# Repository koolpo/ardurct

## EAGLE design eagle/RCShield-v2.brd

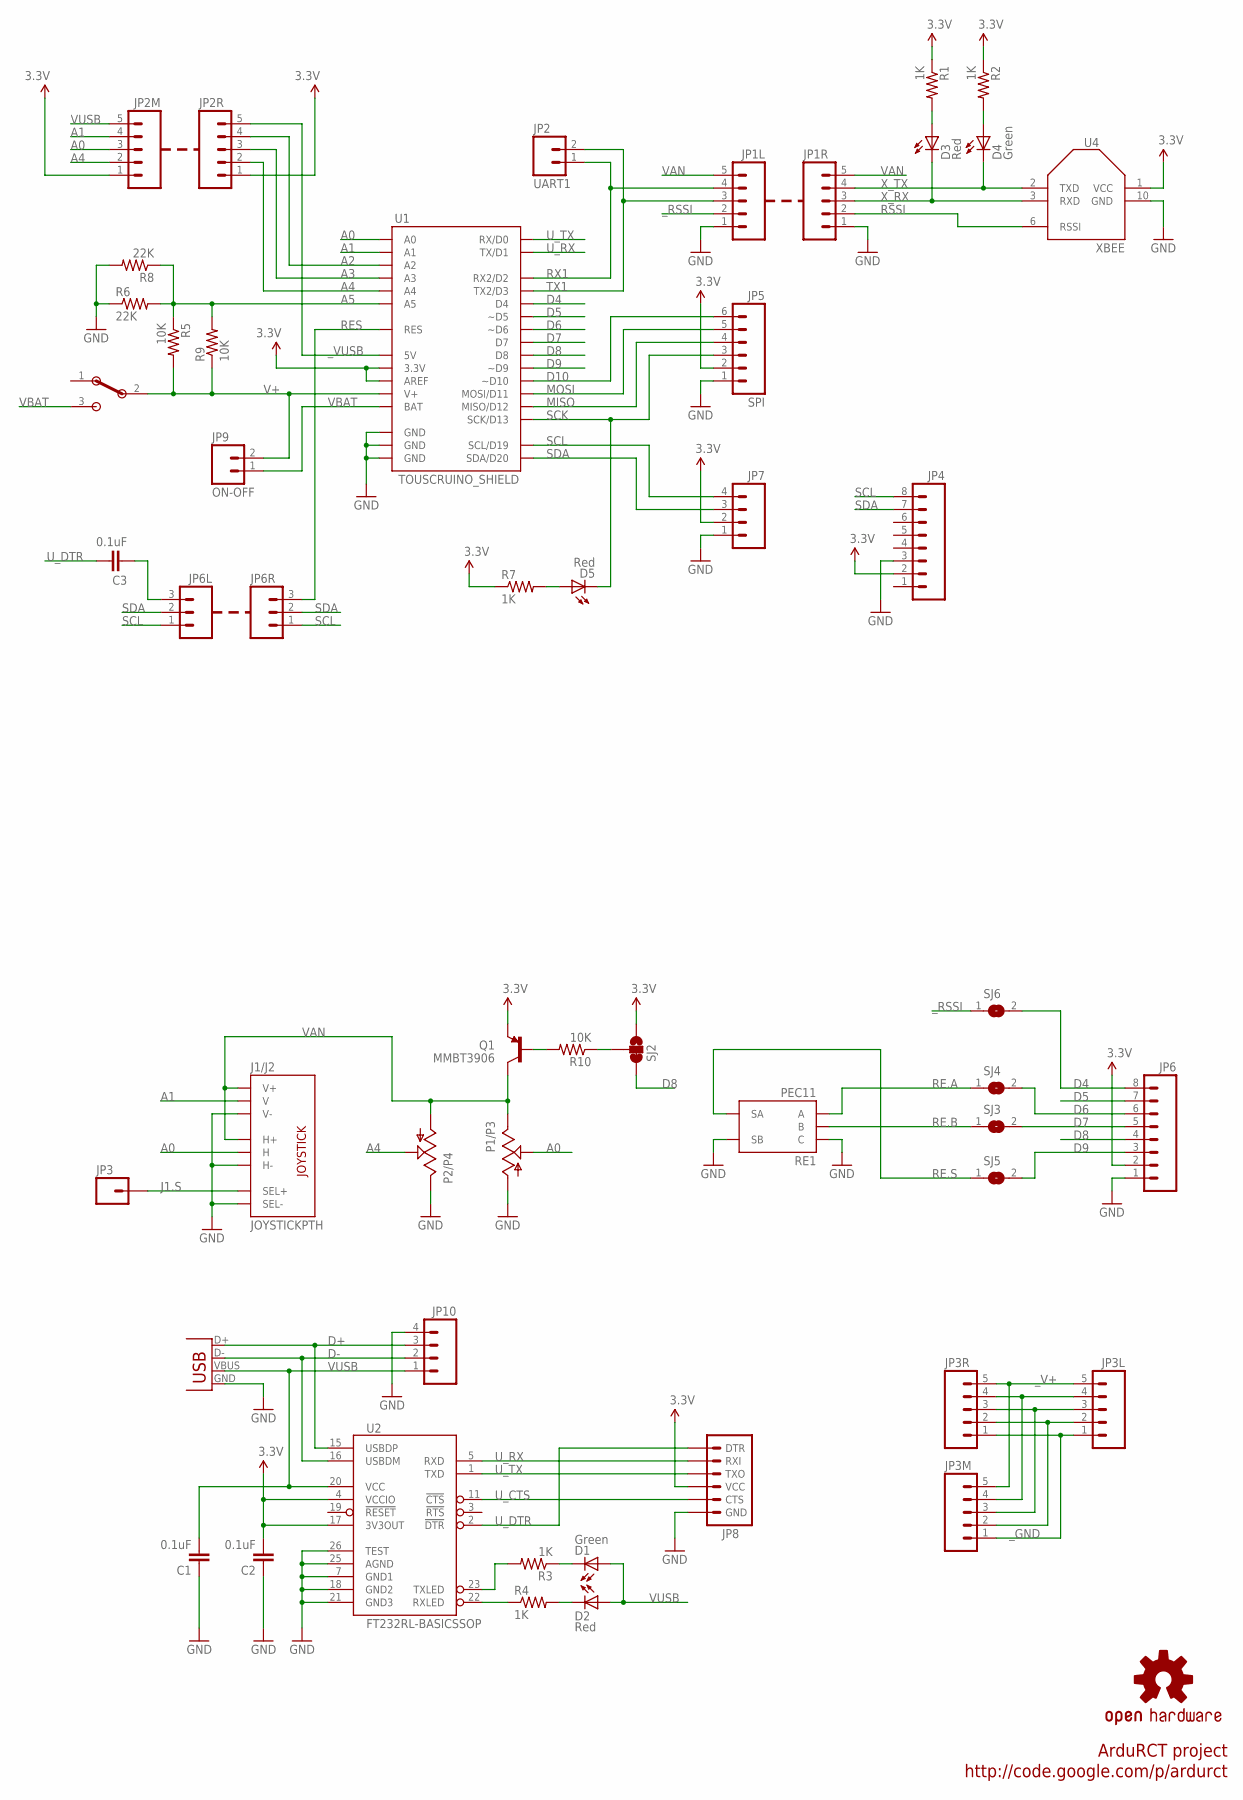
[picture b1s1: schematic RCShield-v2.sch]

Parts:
C1, C2, C3: 0.1uF; 0805
D1, D4: Green; LED
D2, D3, D5: Red; LED
J1/J2: JOYSTICKPTH; JOYSTICK
JP1L, JP1R, JP2M, JP2R, JP3L, JP3M, JP3R: M05; 2+3
JP2: UART1; 1X02
JP3: M01PTH; 1X01
JP4, JP6: M08; 1X08
JP5: SPI; 1X06
JP6L, JP6R: M03PTH; 1X03
JP7, JP10: M04; 1X04
JP8: ARDUINO_SERIAL_PROGRAM; 1X06_F
JP9: ON-OFF; 1X02
P1/P3, P2/P4: POT; ALPS_POT
Q1: MMBT3906; SOT23-3
R1, R2, R3, R4, R7: 1K; 0805
R5, R10: 10K; 0805
R6: 22K; 0805
R8: 22K; 0207/7
R9: 10K; 0207/7
RE1: PEC11
S4: EG1224
SJ2: SJ_2WAYS_1-2W; SJ_2WAYS_1-2
SJ3, SJ4, SJ5, SJ6: SJ
U1: TOUSCRUINO_SHIELD; TOUSCRUINO_SHIELD_SPLIT
U2: FT232RL-BASICSSOP; SSOP28DB
U4: XBEE; XBEE-SMD
U$1: OSHW-LOGOM; OSHW-LOGO-M
X1: USBSMD; USB-MINIB

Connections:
3.3V: C2.2, JP2M.1, JP2R.1, JP4.2, JP5.2, JP6.2, JP7.2, JP8.4 (VCC), Q1.2 (E), R1.1, R2.1, R7.1, SJ2.3, U1.3.3V, U1.AREF, U2.4 (VCCIO), U2.17 (3V3OUT), U4.1 (VCC)
A0: J1/J2.H2 (H), JP2M.3, P1/P3.P$2 (S), U1.A0
A1: J1/J2.V2 (V), JP2M.4, U1.A1
A2: JP2R.4, U1.A2
A3: JP2R.3, U1.A3
A4: JP2M.2, JP2R.2, P2/P4.P$2 (S), U1.A4
A5: R5.1, R6.2, R8.1, R9.2, U1.A5
D4: JP6.8, SJ6.2, U1.D4
D5: JP6.7, U1.D5 (~D5)
D6: JP6.6, SJ4.2, U1.D6 (~D6)
D7: JP6.5, SJ3.2, U1.D7
D8: JP6.4, SJ2.1, U1.D8
D9: JP6.3, SJ5.2, U1.D9 (~D9)
D10: JP5.6, U1.D10 (~D10)
D+: JP10.3, U2.15 (USBDP), X1.D+
D-: JP10.2, U2.16 (USBDM), X1.D-
GND: C1.1, C2.1, J1/J2.B2A (SEL-), J1/J2.H3 (H-), J1/J2.V3 (V-), JP1L.1, JP1R.1, JP4.3, JP5.1, JP6.1, JP7.1, JP8.6 (GND), JP10.4, P1/P3.P$3 (A), P2/P4.P$1 (E), R6.1, R8.2, RE1.C, RE1.S2 (SB), U1.GND@0 (GND), U1.GND@1 (GND), U1.GND@2 (GND), U2.7 (GND1), U2.18 (GND2), U2.21 (GND3), U2.25 (AGND), U2.26 (TEST), U4.10 (GND), X1.GND
J1.S: J1/J2.B1A (SEL+), JP3.1
MISO: JP5.4, U1.D12 (MISO/D12)
MOSI: JP5.5, U1.D11 (MOSI/D11)
unnamed: C3.2, JP6L.3
unnamed: Q1.1 (B), R10.2
unnamed: R10.1, SJ2.2
unnamed: JP3L.4, JP3M.4, JP3R.4
unnamed: JP3L.3, JP3M.3, JP3R.3
unnamed: JP3L.2, JP3M.2, JP3R.2
unnamed: D5.A1 (A), R7.2
unnamed: D3.A1 (A), R1.2
unnamed: R3.2, U2.23 (TXLED)
unnamed: R4.1, U2.22 (RXLED)
unnamed: D4.A1 (A), R2.2
RE.A: RE1.A, SJ4.1
RE.B: RE1.B, SJ3.1
RE.S: RE1.S1 (SA), SJ5.1
RES: JP6R.3, U1.RES
RSSI: JP1R.2, U4.6 (RSSI)
RX1: JP1L.4, JP2.1, U1.D2 (RX2/D2)
SCK: D5.C1 (C), JP5.3, U1.D13 (SCK/D13)
SCL: JP4.8, JP6L.1, JP6R.1, JP7.4, U1.SCL (SCL/D19)
SDA: JP4.7, JP6L.2, JP6R.2, JP7.3, U1.SDA (SDA/D20)
TX1: JP1L.3, JP2.2, U1.D3 (TX2/D3)
U_CTS: JP8.5 (CTS), U2.11 (!CTS)
U_DTR: C3.1, JP8.1 (DTR), U2.2 (!DTR)
U_RX: JP8.2 (RXI), U1.TX (TX/D1), U2.5 (RXD)
U_RX_LED: D2.C1 (C), R4.2
U_TX: JP8.3 (TXO), U1.RX (RX/D0), U2.1 (TXD)
U_TX_LED: D1.C1 (C), R3.1
V+: JP9.2, R5.2, R9.1, S4.2, U1.V+
VAN: J1/J2.H1 (H+), J1/J2.V1 (V+), JP1L.5, JP1R.5, P1/P3.P$1 (E), P2/P4.P$3 (A), Q1.3 (C)
VBAT: JP9.1, S4.3, U1.BAT
VUSB: C1.2, D1.A1 (A), D2.A1 (A), JP2M.5, JP10.1, U2.20 (VCC), X1.VBUS
X_RX: D3.C1 (C), JP1R.3, U4.3 (RXD)
X_TX: D4.C1 (C), JP1R.4, U4.2 (TXD)
_GND: JP3L.1, JP3M.1, JP3R.1
_RSSI: JP1L.2, SJ6.1
_V+: JP3L.5, JP3M.5, JP3R.5
_VUSB: JP2R.5, U1.5V

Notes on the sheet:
ArduRCT project
http://code.google.com/p/ardurct

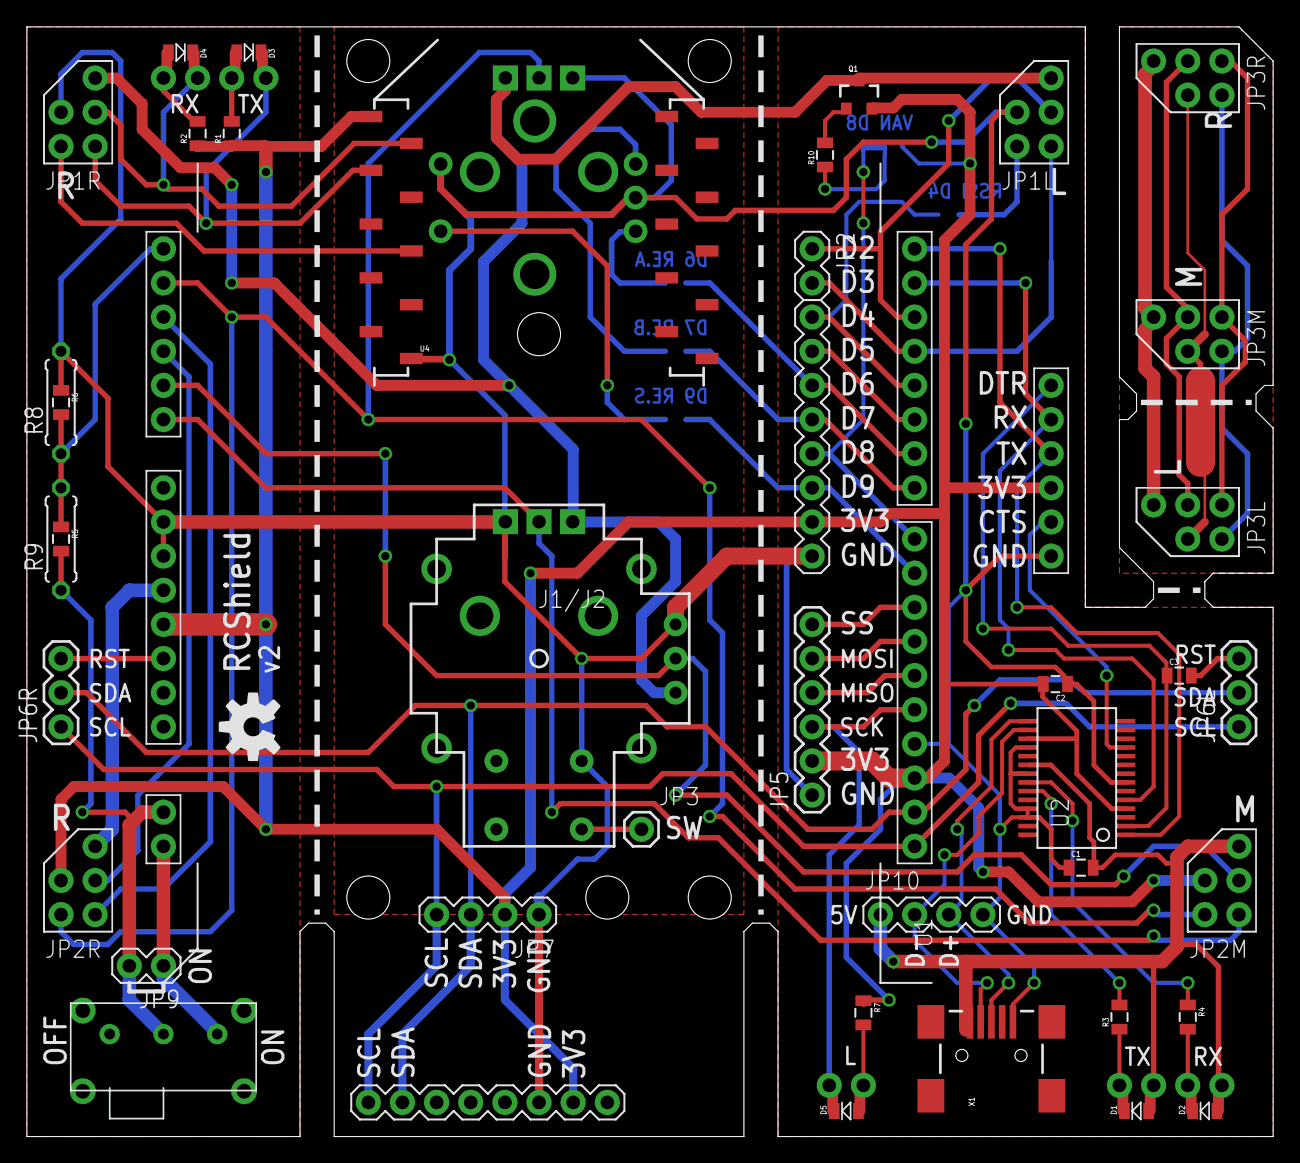
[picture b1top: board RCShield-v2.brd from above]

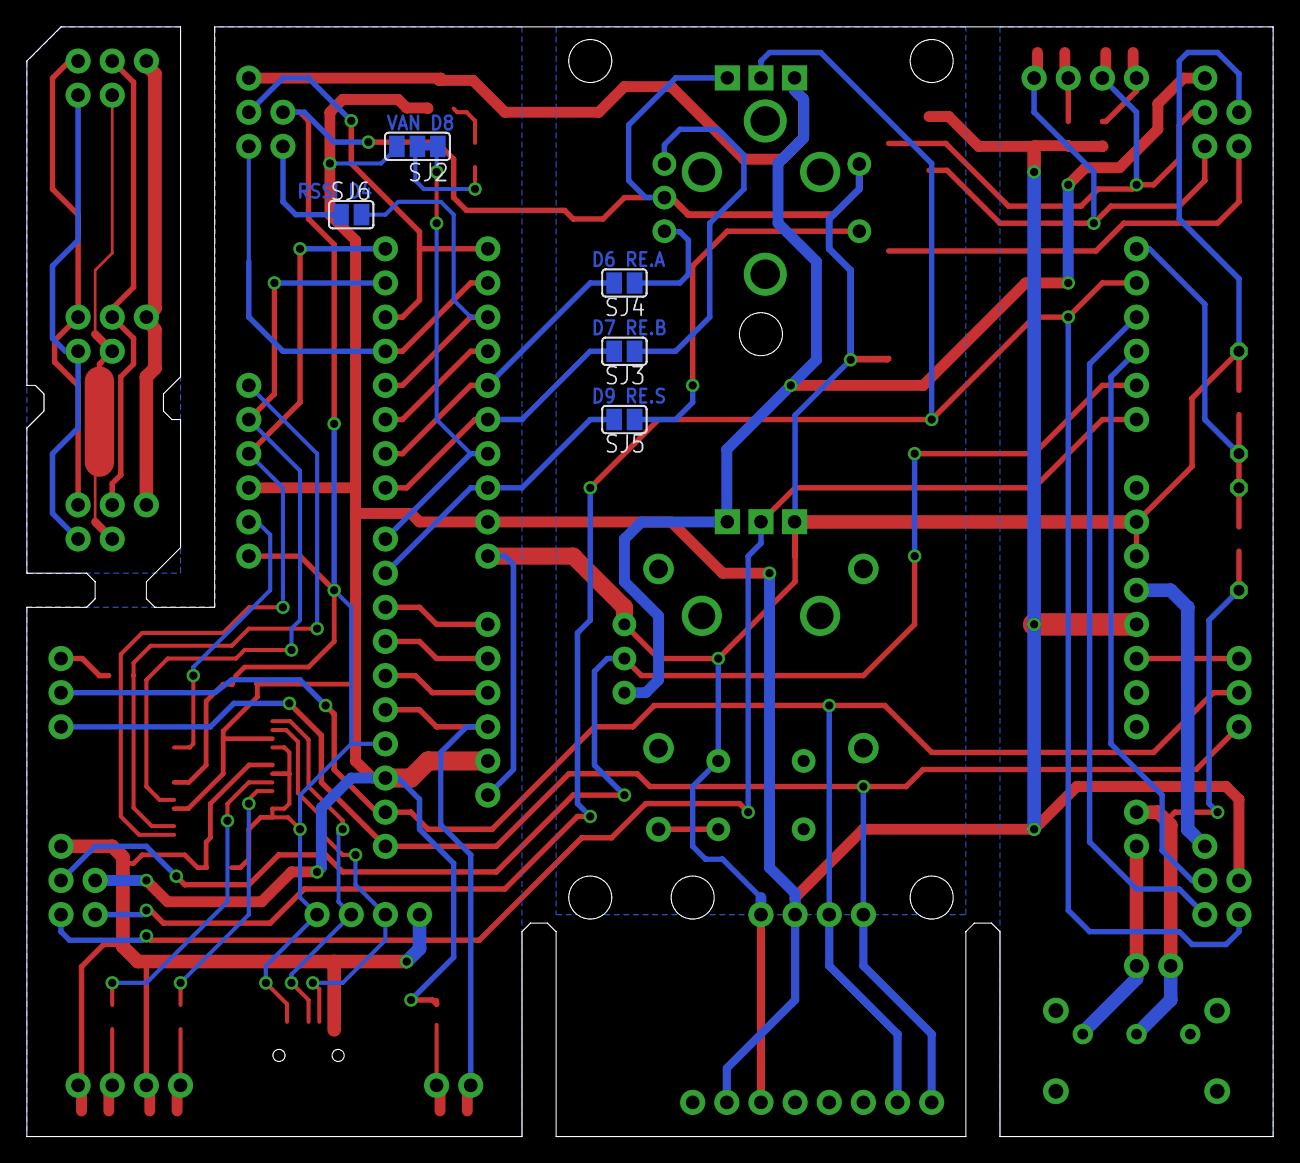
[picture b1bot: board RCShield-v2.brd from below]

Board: 2 copper layers, 92.7 x 82.5 mm, 52 parts (5 on the bottom side), 57 nets.

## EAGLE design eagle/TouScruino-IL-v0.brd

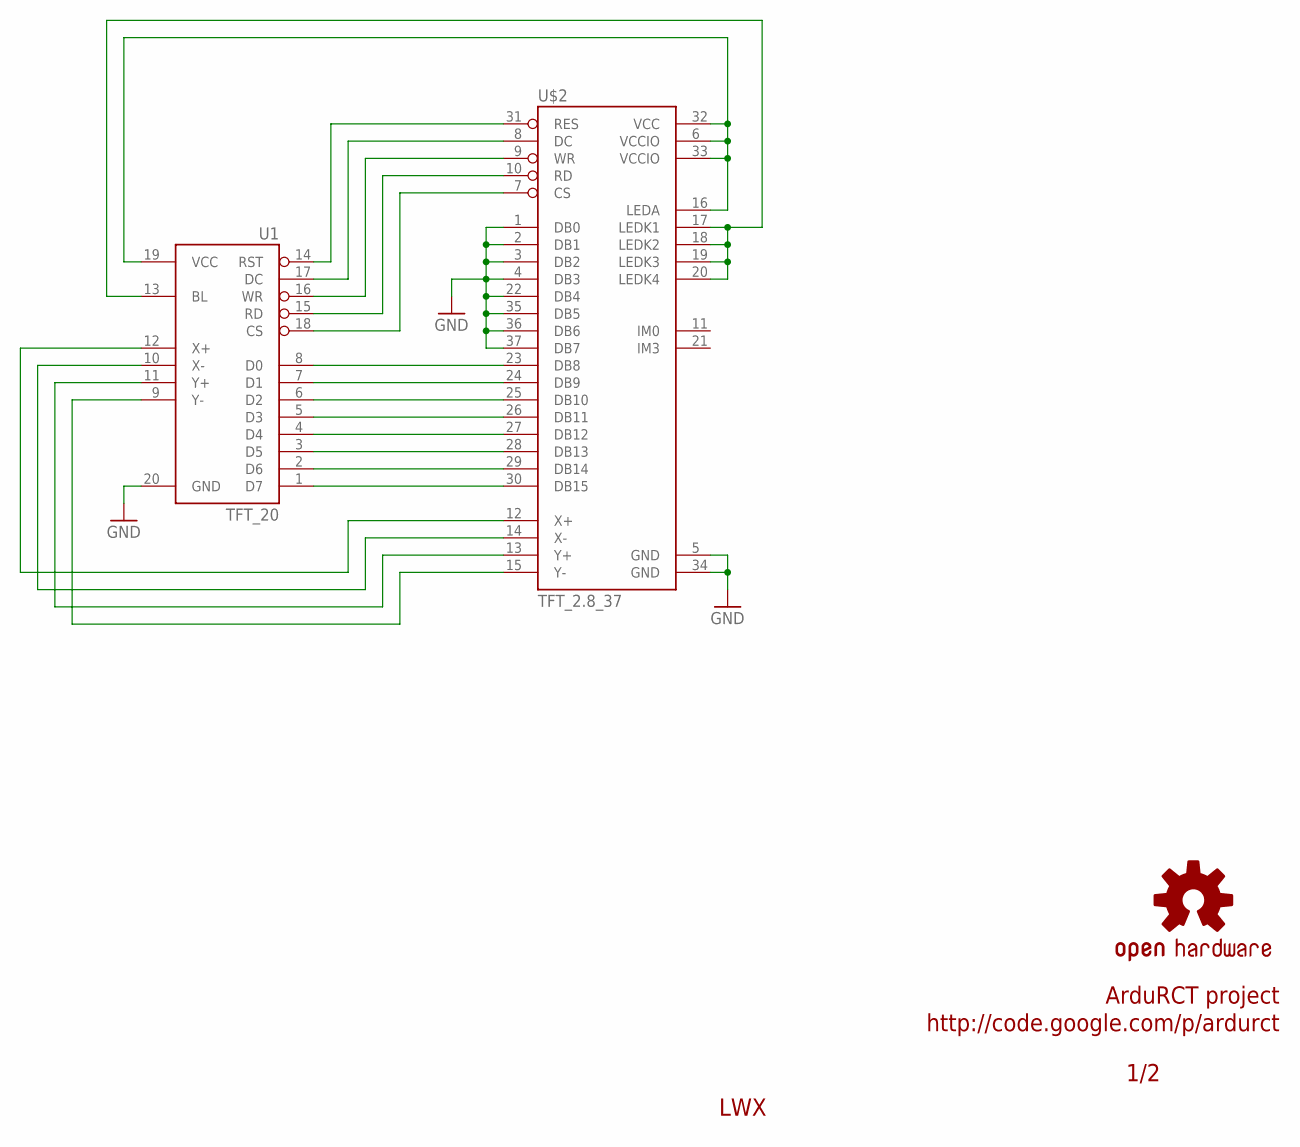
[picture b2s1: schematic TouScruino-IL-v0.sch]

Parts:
U1: TFT_20; 1X20
U$2: TFT_2.8_37
U$3: OSHW-LOGOM; OSHW-LOGO-M

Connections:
GND: U1.20 (GND), U$2.1 (DB0), U$2.2 (DB1), U$2.3 (DB2), U$2.4 (DB3), U$2.5 (GND), U$2.22 (DB4), U$2.34 (GND), U$2.35 (DB5), U$2.36 (DB6), U$2.37 (DB7)
unnamed: U1.19 (VCC), U$2.6 (VCCIO), U$2.16 (LEDA), U$2.32 (VCC), U$2.33 (VCCIO)
unnamed: U1.13 (BL), U$2.17 (LEDK1), U$2.18 (LEDK2), U$2.19 (LEDK3), U$2.20 (LEDK4)
unnamed: U1.8 (D0), U$2.23 (DB8)
unnamed: U1.7 (D1), U$2.24 (DB9)
unnamed: U1.9 (Y-), U$2.15 (Y-)
unnamed: U1.11 (Y+), U$2.13 (Y+)
unnamed: U1.10 (X-), U$2.14 (X-)
unnamed: U1.12 (X+), U$2.12 (X+)
unnamed: U1.14 (RST), U$2.31 (RES)
unnamed: U1.17 (DC), U$2.8 (DC)
unnamed: U1.16 (WR), U$2.9 (WR)
unnamed: U1.15 (RD), U$2.10 (RD)
unnamed: U1.18 (CS), U$2.7 (CS)
unnamed: U1.6 (D2), U$2.25 (DB10)
unnamed: U1.5 (D3), U$2.26 (DB11)
unnamed: U1.4 (D4), U$2.27 (DB12)
unnamed: U1.3 (D5), U$2.28 (DB13)
unnamed: U1.2 (D6), U$2.29 (DB14)
unnamed: U1.1 (D7), U$2.30 (DB15)

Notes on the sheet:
LWX
1/2
ArduRCT project
http://code.google.com/p/ardurct

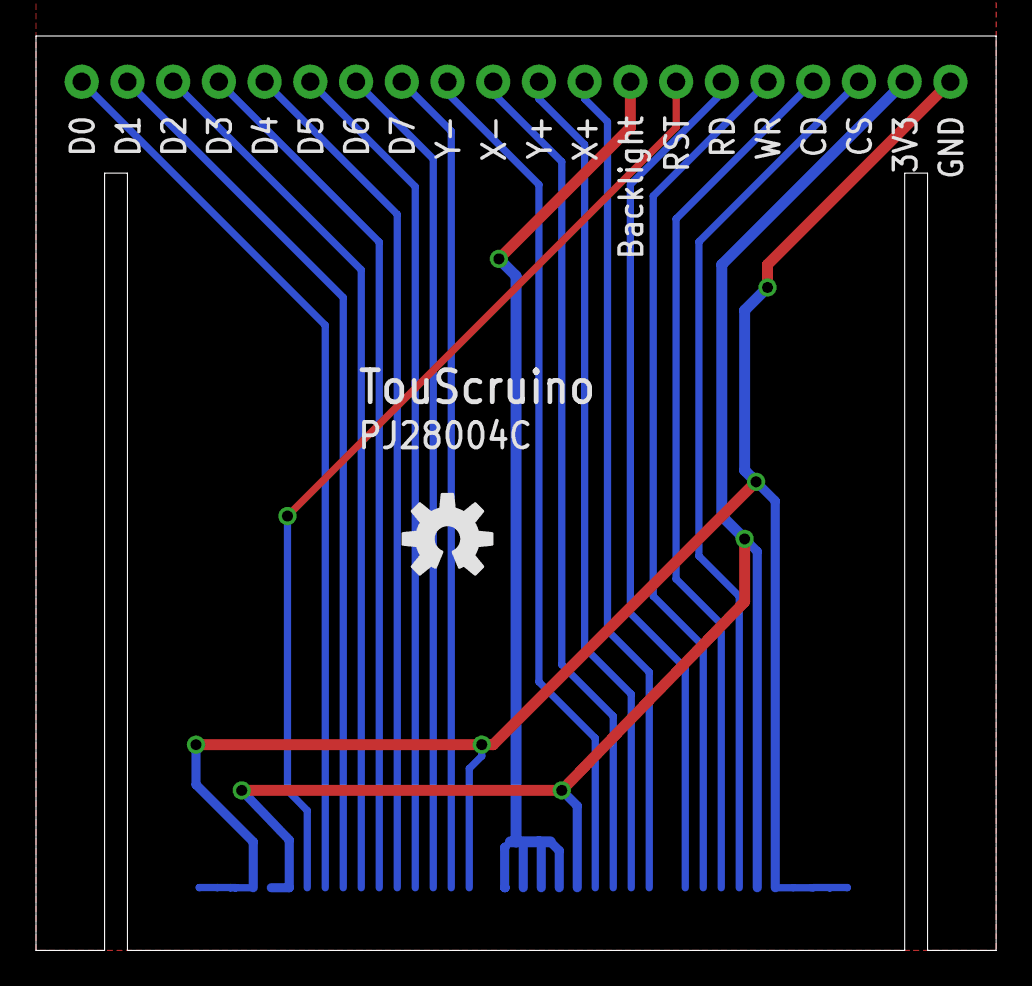
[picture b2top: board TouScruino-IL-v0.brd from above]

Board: 2 copper layers, 53.3 x 50.8 mm, 3 parts (1 on the bottom side), 20 nets.

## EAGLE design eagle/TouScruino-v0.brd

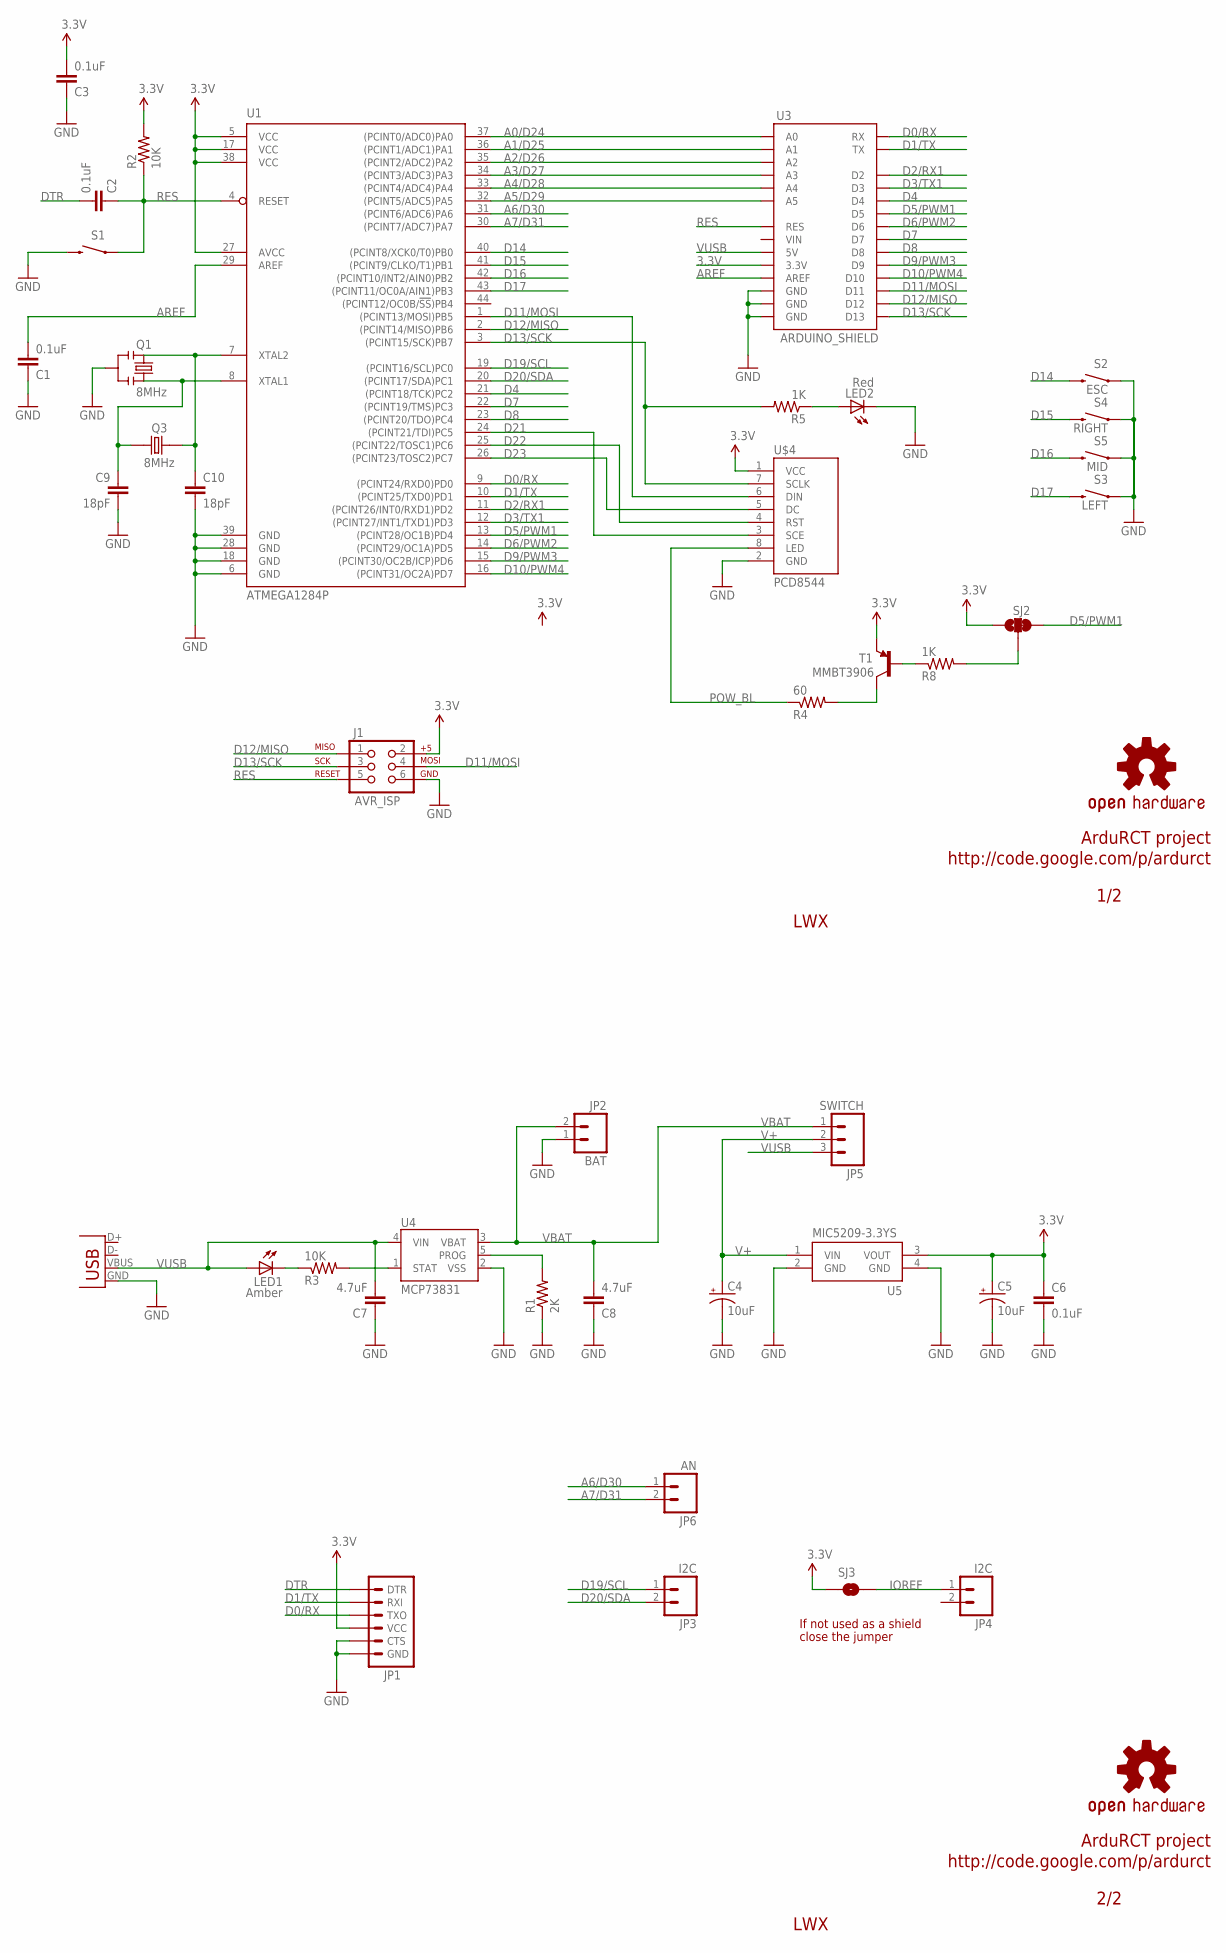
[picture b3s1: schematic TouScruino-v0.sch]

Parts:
C1, C2, C3, C6: 0.1uF; 0805
C4, C5: 10uF; EIA3216
C7, C8: 4.7uF; 0805
C9, C10: 18pF; 0603-CAP
J1: AVR_ISP; 2X3
JP1: ARDUINO_SERIAL_PROGRAMPTH; 1X06
JP2: BAT; JST-2-SMD
JP3, JP4: I2C; 1X02
JP5: SWITCH; 1X3_LONGPAD
JP6: AN; 1X02
LED1: Amber; LED
LED2: Red; LED-0805
Q1: 8MHz; RESONATOR-SMD
Q3: 8MHz; CRYSTAL_5X3.2
R1: 2K; 0805
R2, R3: 10K; 0805
R4: 60; 0805
R5, R8: 1K; 0805
S1: SWITCH-MOMENTARY-2SMD; TACTILE_SWITCH_SMD@1
S2: ESC; TACTILE_SWITCH_SMD
S3: LEFT; TACTILE_SWITCH_SMD
S4: RIGHT; TACTILE_SWITCH_SMD
S5: MID; TACTILE_SWITCH_SMD
SJ2: SJ_2WAYS_1-2; SJ_2WAYS_1-2_S
SJ3: SOLDERJUMPERNO; SJ_2S-NO
T1: MMBT3906; SOT23-3
U1: ATMEGA1284P; TQFP44
U3: ARDUINO_SHIELD
U4: MCP73831; SOT23-5
U5: MIC5209-3.3YS; SOT223
U$3, U$5: OSHW-LOGOM; OSHW-LOGO-M
U$4: PCD8544
X1: USBSMD; USB-MINIB

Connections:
3.3V: C3.2, C5.A (+), C6.1, J1.2, JP1.4 (VCC), R2.2, SJ2.3, SJ3.1, T1.2 (E), U1.5 (VCC), U1.17 (VCC), U1.27 (AVCC), U1.38 (VCC), U3.3.3V, U5.3 (VOUT), U$4.1 (VCC)
A0/D24: U1.37 ((PCINT0/ADC0)PA0), U3.A0
A1/D25: U1.36 ((PCINT1/ADC1)PA1), U3.A1
A2/D26: U1.35 ((PCINT2/ADC2)PA2), U3.A2
A3/D27: U1.34 ((PCINT3/ADC3)PA3), U3.A3
A4/D28: U1.33 ((PCINT4/ADC4)PA4), U3.A4
A5/D29: U1.32 ((PCINT5/ADC5)PA5), U3.A5
A6/D30: JP6.1, U1.31 ((PCINT6/ADC6)PA6)
A7/D31: JP6.2, U1.30 ((PCINT7/ADC7)PA7)
AREF: C1.2, U1.29 (AREF), U3.AREF
BL_CMD: R8.2, SJ2.2
D0/RX: JP1.3 (TXO), U1.9 ((PCINT24/RXD0)PD0), U3.RX
D1/TX: JP1.2 (RXI), U1.10 ((PCINT25/TXD0)PD1), U3.TX
D2/RX1: U1.11 ((PCINT26/INT0/RXD1)PD2), U3.D2
D3/TX1: U1.12 ((PCINT27/INT1/TXD1)PD3), U3.D3
D4: U1.21 ((PCINT18/TCK)PC2), U3.D4
D5/PWM1: SJ2.1, U1.13 ((PCINT28/OC1B)PD4), U3.D5
D6/PWM2: U1.14 ((PCINT29/OC1A)PD5), U3.D6
D7: U1.22 ((PCINT19/TMS)PC3), U3.D7
D8: U1.23 ((PCINT20/TDO)PC4), U3.D8
D9/PWM3: U1.15 ((PCINT30/OC2B/ICP)PD6), U3.D9
D10/PWM4: U1.16 ((PCINT31/OC2A)PD7), U3.D10
D11/MOSI: J1.4, U1.1 ((PCINT13/MOSI)PB5), U3.D11, U$4.6 (DIN)
D12/MISO: J1.1, U1.2 ((PCINT14/MISO)PB6), U3.D12
D13/SCK: J1.3, R5.2, U1.3 ((PCINT15/SCK)PB7), U3.D13, U$4.7 (SCLK)
D14: S2.3 (2), U1.40 ((PCINT8/XCK0/T0)PB0)
D15: S4.3 (2), U1.41 ((PCINT9/CLKO/T1)PB1)
D16: S5.3 (2), U1.42 ((PCINT10/INT2/AIN0)PB2)
D17: S3.3 (2), U1.43 ((PCINT11/OC0A/AIN1)PB3)
D19/SCL: JP3.1, U1.19 ((PCINT16/SCL)PC0)
D20/SDA: JP3.2, U1.20 ((PCINT17/SDA)PC1)
D21: U1.24 ((PCINT21/TDI)PC5), U$4.3 (SCE)
D22: U1.25 ((PCINT22/TOSC1)PC6), U$4.4 (RST)
D23: U1.26 ((PCINT23/TOSC2)PC7), U$4.5 (DC)
DTR: C2.2, JP1.1 (DTR)
GND: C1.1, C3.1, C4.C (-), C5.C (-), C6.2, C7.1, C8.1, C9.2, C10.2, J1.6, JP1.5 (CTS), JP1.6 (GND), JP2.1, LED2.2 (C), Q1.2, R1.1, S1.3 (2), S2.1, S3.1, S4.1, S5.1, U1.6 (GND), U1.18 (GND), U1.28 (GND), U1.39 (GND), U3.GND@0 (GND), U3.GND@1 (GND), U3.GND@2 (GND), U4.2 (VSS), U5.2 (GND), U5.4 (GND), U$4.2 (GND), X1.GND
IOREF: JP4.1, SJ3.2
unnamed: C9.1, Q1.1, Q3.2, U1.8 (XTAL1)
unnamed: C10.1, Q1.3, Q3.1, U1.7 (XTAL2)
unnamed: LED2.1 (A), R5.1
unnamed: LED1.C1 (C), R3.1
unnamed: R3.2, U4.1 (STAT)
unnamed: R1.2, U4.5 (PROG)
unnamed: R4.2, T1.3 (C)
unnamed: R8.1, T1.1 (B)
POW_BL: R4.1, U$4.8 (LED)
RES: C2.1, J1.5, R2.1, S1.1, U1.4 (RESET), U3.RES
V+: C4.A (+), JP5.2, U5.1 (VIN)
VBAT: C8.2, JP2.2, JP5.1, U4.3 (VBAT)
VUSB: C7.2, JP5.3, LED1.A1 (A), U3.5V, U4.4 (VIN), X1.VBUS

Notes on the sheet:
LWX
1/2
2/2
If not used as a shield
close the jumper
ArduRCT project
http://code.google.com/p/ardurct

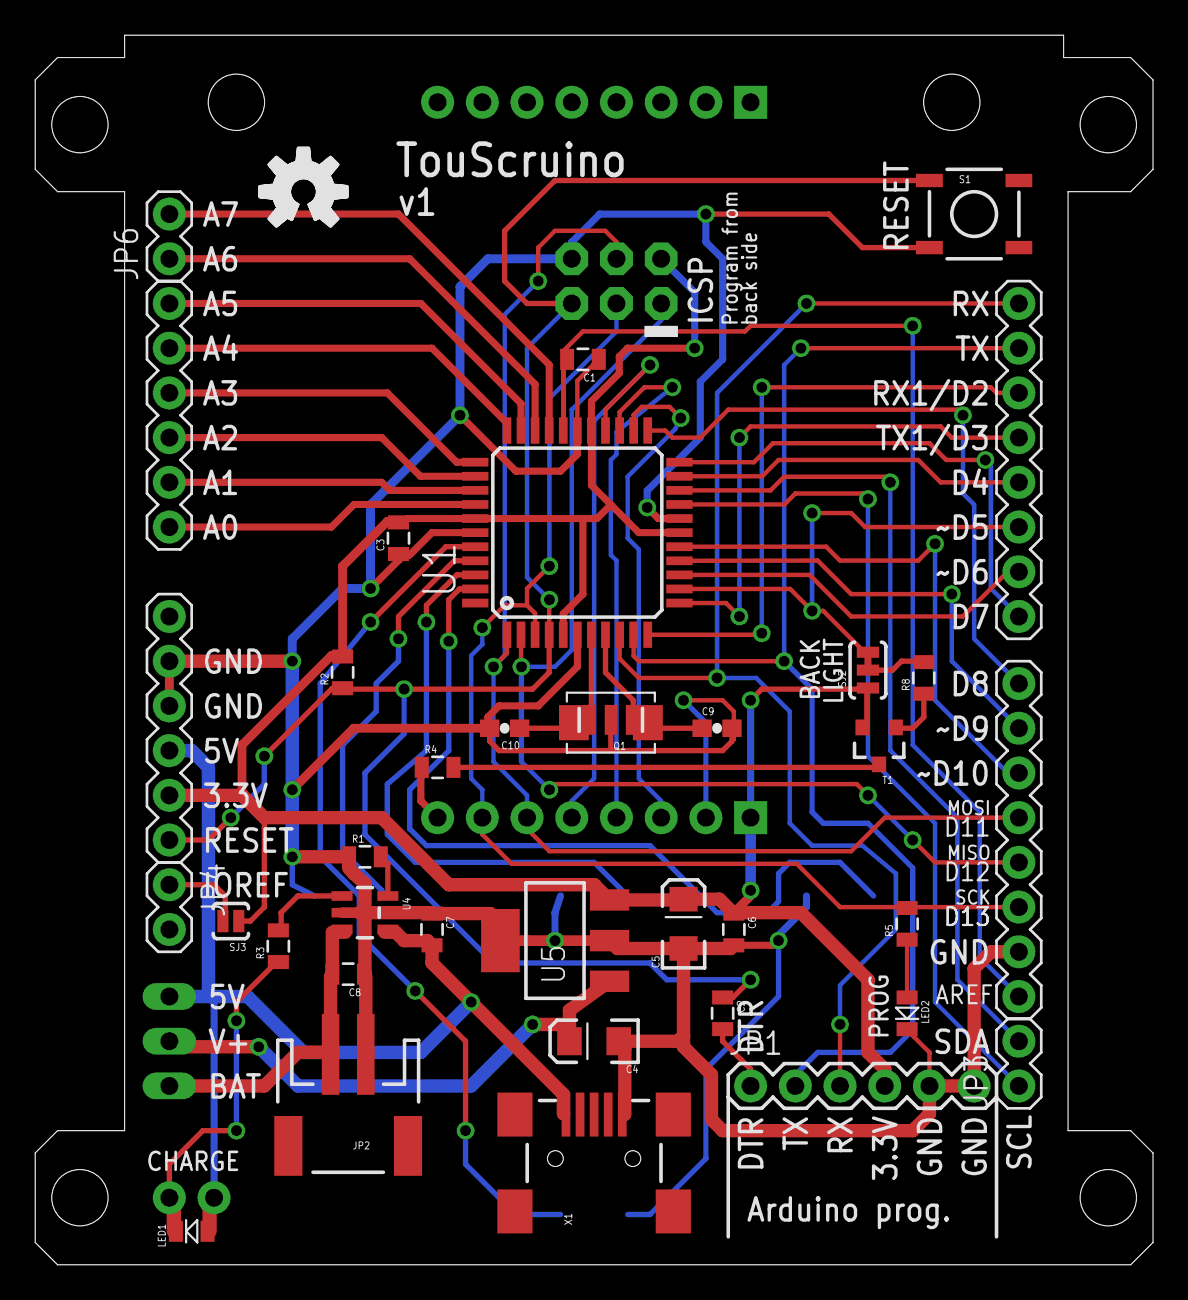
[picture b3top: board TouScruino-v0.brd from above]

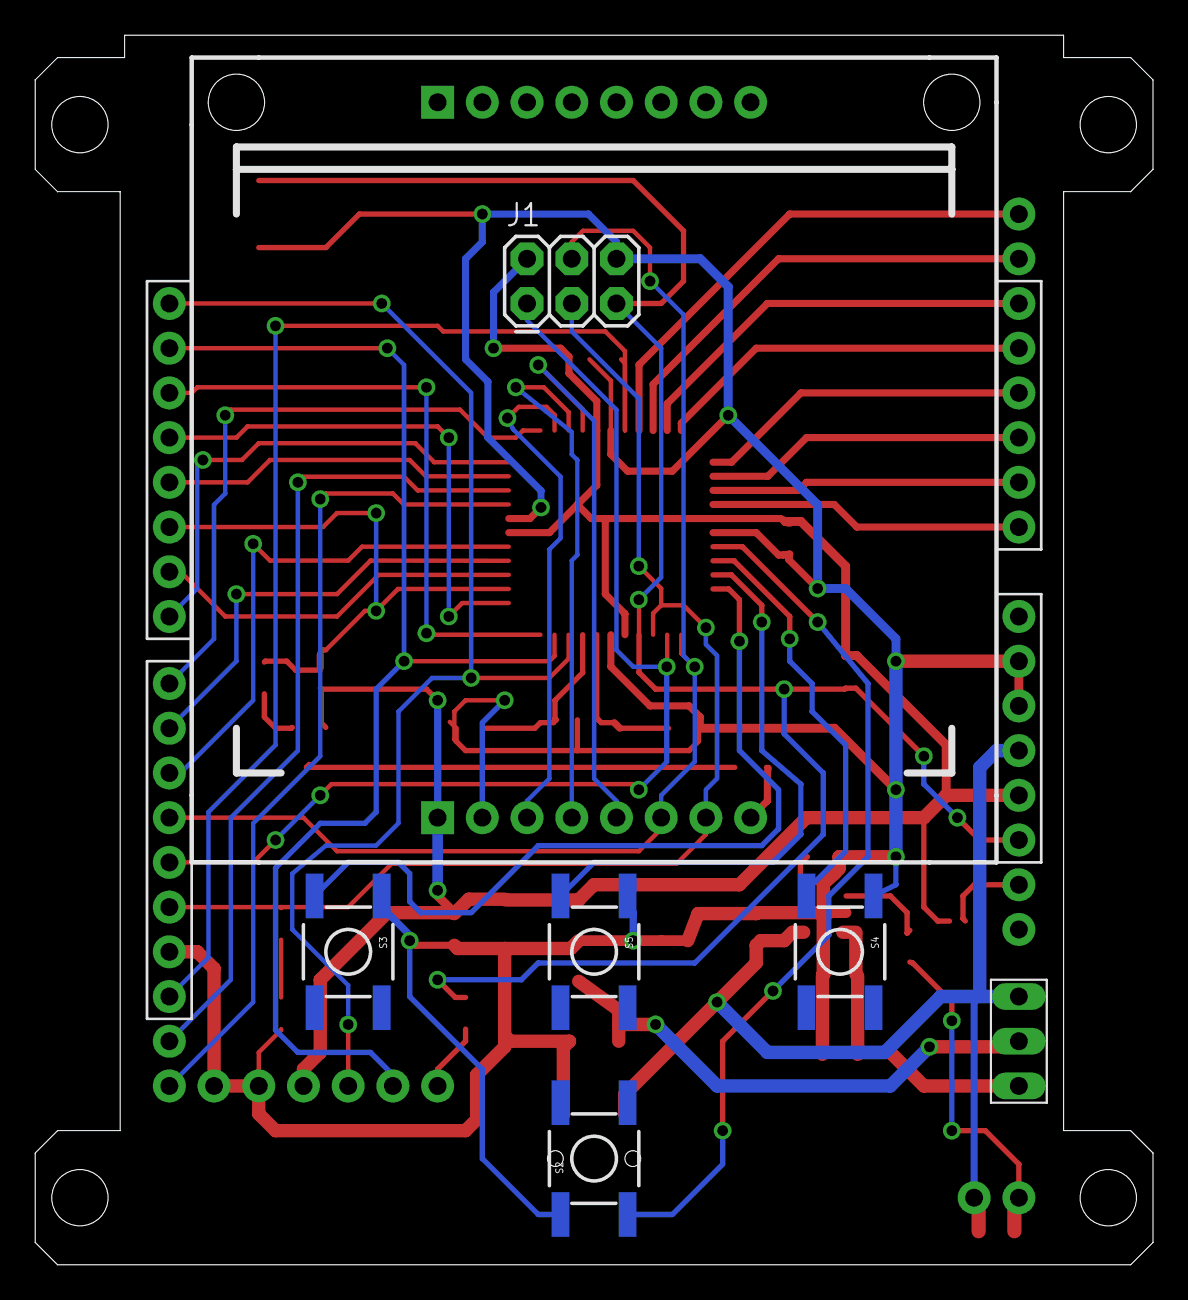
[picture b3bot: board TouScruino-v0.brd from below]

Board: 2 copper layers, 63.5 x 69.8 mm, 43 parts (8 on the bottom side), 50 nets.
